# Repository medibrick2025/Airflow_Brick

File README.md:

# Airflow / Spiro Brick

The Spiro Brick interfaces with the [Sensirion SFM3300-D](https://sensirion.com/products/catalog/SFM3300-D) airflow sensor. It also enables airway pressure measurement using Amphenol differential pressure sensor such as [ELVH-family](https://allsensors.com/en/product-listing?family=elvh) with I2C 3.3V or 5V interface.

- [Datasheet SFM3300](./datasheets/Sensirion_Datasheet_SFM3300-AW_SFM3300-D.pdf)
- [Datasheet ELVH Family](./datasheets/DS-0376.pdf)

Example differential pressure sensor with I2C and 5V interface: ELVH-M160D-HRRD-C-N2A5 for 1/16 ID 1/8 OD tubing.

## Documentation

- [Education Background](./spirometer%20educational%20background/)
- [Assembly Instructions](./Spirometer%20Mechanical%20Design%20And%20Mechanical%20Assembly/)
- [Software / Firmware](./Spirometer%20Software/)

## SFM3300

- [Cleaning](./datasheets/Sensirion_GF_AN_SFM-21_Cleaning_Methods_D1.pdf)
- [Eval Kit](./datasheets/Sensirion_GF_AN_SFM-22_ClipOn_CapCable_Evaluation_Kit_D1_1.pdf)
- [Arduino Driver Sensirion](https://github.com/Sensirion/arduino-i2c-sfm3000) with [Sensirion Arduino Core](https://github.com/Sensirion/arduino-core)
- [Arduino Driver Alternative](https://github.com/MyElectrons/sfm3300-arduino)
 
## Spiro Brick PCB Design

The following files were created for this project using KiCad.

[View schematics as PDF](./KiCad/Altekreeti/Spiro_Brick.pdf)

## LiPo to 5V Power Boost

- [Ti TPS61090 Eval](./reference_designs/TPS61090_sbvu003.pdf)
- [Adafruit](https://learn.adafruit.com/adafruit-powerboost-500-plus-charger/downloads)

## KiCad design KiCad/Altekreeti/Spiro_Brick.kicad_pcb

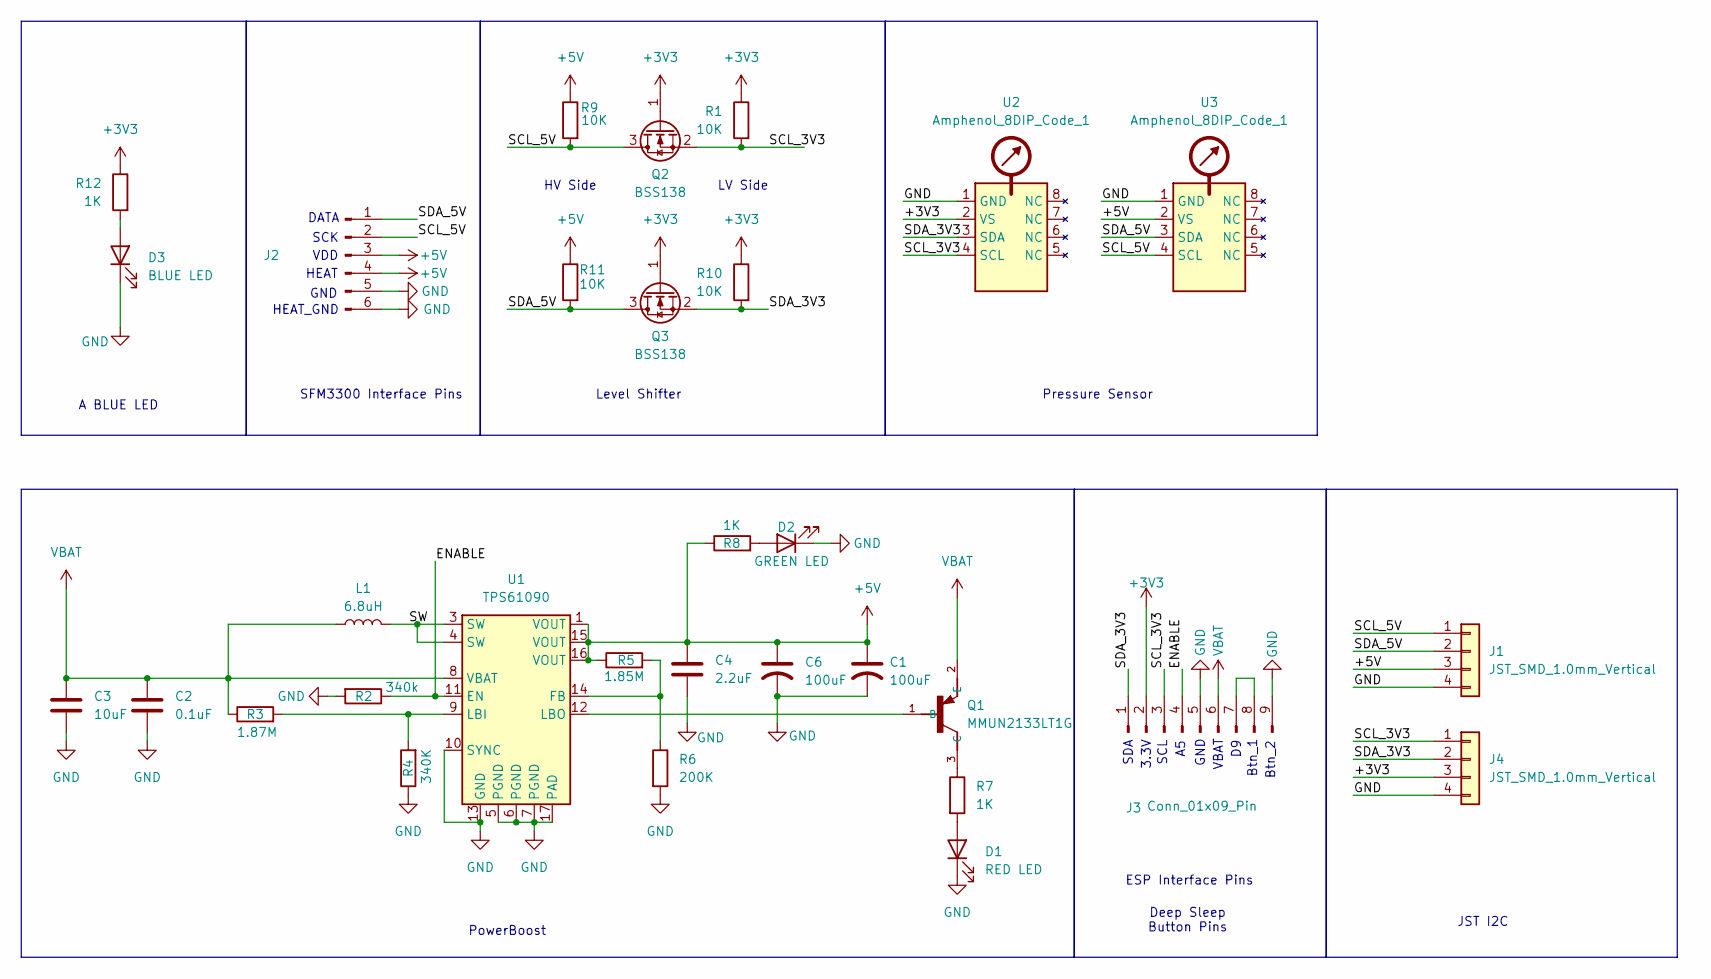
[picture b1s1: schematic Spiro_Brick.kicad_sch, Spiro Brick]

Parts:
C1, C6: 100uF; C_1210_3225Metric_Pad1.33x2.70mm_HandSolder
C2: 0.1uF; C_0805_2012Metric_Pad1.18x1.45mm_HandSolder
C3: 10uF; C_0805_2012Metric_Pad1.18x1.45mm_HandSolder
C4: 2.2uF; C_0805_2012Metric_Pad1.18x1.45mm_HandSolder
D1: RED LED; LED_0805_2012Metric
D2: GREEN LED; LED_0805_2012Metric
D3: BLUE LED; LED_0805_2012Metric
J1, J4: JST_SMD_1.0mm_Vertical; JST_1x04_P1.0mm_Vertical_SMD
J2: PinHeader_1x06_P2.54mm_Vertical
J3: Conn_01x09_Pin; PinHeader_1x09_P2.54mm_Vertical
L1: 6.8uH; L_Changjiang_FNR5045S
Q1: MMUN2133LT1G; SOT95P240X111-3N
Q2, Q3: BSS138; SOT-23
R1, R9, R10, R11: 10K; R_0805_2012Metric_Pad1.20x1.40mm_HandSolder
R2: 340k; R_0805_2012Metric_Pad1.20x1.40mm_HandSolder
R3: 1.87M; R_0805_2012Metric_Pad1.20x1.40mm_HandSolder
R4: 340K; R_0805_2012Metric_Pad1.20x1.40mm_HandSolder
R5: 1.85M; R_0805_2012Metric_Pad1.20x1.40mm_HandSolder
R6: 200K; R_0805_2012Metric_Pad1.20x1.40mm_HandSolder
R7, R8, R12: 1K; R_0805_2012Metric_Pad1.20x1.40mm_HandSolder
U1: TPS61090; Texas_RSA_VQFN-16-1EP_4x4mm_P0.65mm_EP2.7x2.7mm_ThermalVias
U2, U3: Amphenol_8DIP_Code_1; Amphenol_DIP-8_W13.08mm

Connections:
+3V3: J3.2, J4.3, Q2.1 (G), Q3.1 (G), R1.1, R10.1, R12.1, U2.2 (VS)
+5V: C1.1, C4.1, C6.1, J1.3, J2.3, J2.4, R5.1, R8.1, R9.1, R11.1, U1.1 (VOUT), U1.15 (VOUT), U1.16 (VOUT), U3.2 (VS)
/ENABLE: J3.4, R2.1, U1.11 (EN)
/SCL_3V3: J3.3, J4.1, Q2.2 (S), R1.2, U2.4 (SCL)
/SCL_5V: J1.1, J2.2, Q2.3 (D), R9.2, U3.4 (SCL)
/SDA_3V3: J3.1, J4.2, Q3.2 (S), R10.2, U2.3 (SDA)
/SDA_5V: J1.2, J2.1, Q3.3 (D), R11.2, U3.3 (SDA)
/SW: L1.2, U1.3 (SW), U1.4 (SW)
GND: C1.2, C2.2, C3.2, C4.2, C6.2, D1.1 (K), D2.1 (K), D3.1 (K), J1.4, J2.5, J2.6, J3.5, J3.9, J4.4, R2.2, R4.1, R6.2, U1.5 (PGND), U1.6 (PGND), U1.7 (PGND), U1.10 (SYNC), U1.13 (GND), U1.17 (PAD), U2.1 (GND), U3.1 (GND)
unnamed: D1.2 (A), R7.2
unnamed: D2.2 (A), R8.2
unnamed: D3.2 (A), R12.2
unnamed: J3.7, J3.8
unnamed: Q1.1 (B), U1.12 (LBO)
unnamed: Q1.3 (C), R7.1
unnamed: R5.2, R6.1, U1.14 (FB)
unnamed: R3.2, R4.2, U1.9 (LBI)
VBAT: C2.1, C3.1, J3.6, L1.1, Q1.2 (E), R3.1, U1.8 (VBAT)

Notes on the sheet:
HEAT
SDA
ESP Interface Pins
SFM3300 Interface Pins
Level Shifter
SCK
SCL
HV Side
Deep Sleep Button Pins
Btn_1
Btn_2
LV Side
DATA
Pressure Sensor
GND
VBAT
PowerBoost
A BLUE LED
3.3V
VDD
JST I2C
HEAT_GND

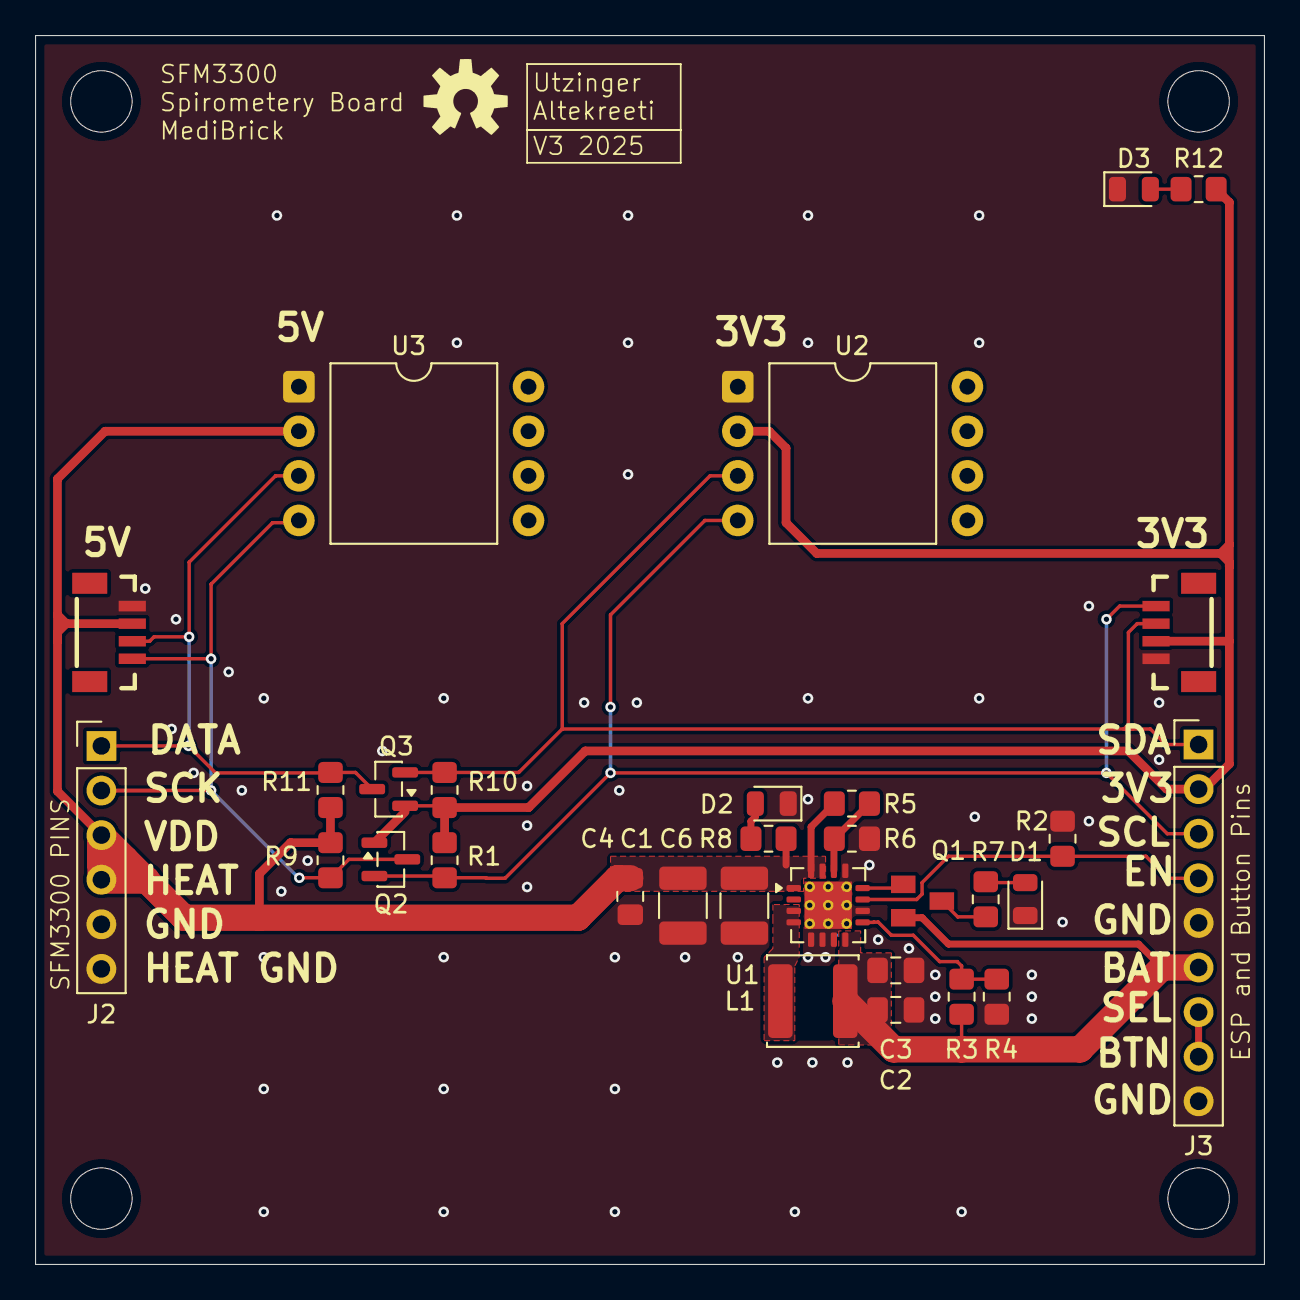
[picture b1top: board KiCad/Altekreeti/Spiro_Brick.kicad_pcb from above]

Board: 2 copper layers, 70.0 x 70.0 mm, 31 parts (0 on the bottom side), 18 nets.

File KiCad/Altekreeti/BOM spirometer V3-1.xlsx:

Item # | Designator | Qty | Manufacturer | Mfg Part # | LCSC Part# | U.S. Distributor | Description / Value | Packaging | Type | Cost | Designation | Footprint | Remark
1 | Q2,Q3 | 2 | onsemi | BSS138 | C52895 |  | N-Channel 50V 0.22A 0.36W Surface Mount SOT-23 | SOT-23 | SMD | 6.1199999999999997E-2 | BSS138 | SOT-23
2 | C1,C6 | 2 | YAGEO | CC1210MKX5R6BB107 | C723734 |  | 100uF ±20% 10V Ceramic Capacitor X5R 1210 | 1210 | SMD | 0.67759999999999998 | 100uF | C_1210_3225Metric_Pad1.33x2.70mm
3 | R7,R8,R12 | 2 | YAGEO | RC0805FR-071KL | C95781 |  | RES 1kΩ ±1% 125mW 0805 | 805 | SMD | 2E-3 | 1K | R_0805_2012Metric_Pad1.20x1.40mm
4 | L1 | 1 | cjiang | FNR5040S6R8MT | C167965 |  | 6.8uH Magnetic Shielded Inductor 3.4A SMD,5x5mm Fixed Inductors RoHS | 5x5mm | SMD | 9.3299999999999994E-2 | 6.8uH | L_Changjiang_FNR5045S
5 | C4 | 1 | YAGEO | CC0805KKX5R8BB225 | C277526 |  | 2.2uF ±10% 25V Ceramic Capacitor X5R 0805 | 805 | SMD | 1.84E-2 | 2.2uF | C_0805_2012Metric_Pad1.18x1.45mm
6 | D2 | 1 | XINGLIGHT | XL-2012UGC | C965815 |  | Green LED | 805 | SMD | 5.7000000000000002E-3 | GRN | LED_0805_2012Metric_GREEN_COLOR
7 | R4 | 1 | YAGEO | RC0805FR-07340KL | C137543 |  | RES 340kΩ ±1% 125mW | 805 | SMD | 2.0999999999999999E-3 | 340K | R_0805_2012Metric_Pad1.20x1.40mm
8 | R2 | 1 | YAGEO | RC0805FR-07100KL | C96346 |  | RES 100kΩ ±1% 125mW 0805 | 805 | SMD | 2.5000000000000001E-3 | 100k | R_0805_2012Metric_Pad1.20x1.40mm
9 | C3 | 1 | Samsung Electro-Mechanics | CL21A106KBYQNNE | C2932476 |  | 10uF ±10% 50V Ceramic Capacitor X5R 0805 | 805 | SMD | 4.1399999999999999E-2 | 10uF | C_0805_2012Metric_Pad1.18x1.45mm
10 | R5 | 1 | Walsin | WR08W1804FTL | C170816 |  | RES 1.8MΩ ±1% 125mW 0805 | 805 | SMD | 5.4000000000000003E-3 | 1.80M | R_0805_2012Metric_Pad1.20x1.40mm
11 | Q1 | 1 | onsemi | MMUN2133LT1G | C86182 |  | Pre-Biased Bipolar Transistor (BJT) 50V 100mA 246mW Surface Mount SOT-23 | SOT-23 | SMD | 3.0599999999999999E-2 | MMUN2133LT1G | SOT95P240X111-3N
12 | R11,R9,R1,R10 | 4 | YAGEO | RC0805FR-0710KL | C84376 |  | RES 10kΩ ±1% 125mW | 805 | SMD | 1.9E-3 | 10K | R_0805_2012Metric_Pad1.20x1.40mm
13 | R3 | 1 | Walsin | WR08W1874FTL | C367830 |  | RES 1.87MΩ ±1% 125mW 0805 | 805 | SMD | 5.3E-3 | 1.87M | R_0805_2012Metric_Pad1.20x1.40mm
14 | U1 | 1 | TI | TPS61030RSAR | C10110 |  | 600kHz Boost Adjustable 1.8V~5.5V 1A QFN-16-EP(4x4) Voltage Regulators - DC DC 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 | QFN-16-EP(4x4) | SMD | 1.6899 | TPS61090 | Texas_RSA_VQFN-16-1EP_4x4mm_P0.65mm_EP2.7x2.7mm_ThermalVias
15 | D1 | 1 | XINGLIGHT | XL-2012SURC | C965812 |  | RED LED | 805 | SMD | 5.8999999999999999E-3 | RED LED | LED_0805_2012Metric_RED_COLOR
16 | R6 | 1 | YAGEO | RT0805BRD07200KL | C728645 |  | RES 200kΩ ±0.1% 125mW 0805 | 805 | SMD | 3.3599999999999998E-2 | 200K | R_0805_2012Metric_Pad1.20x1.40mm
17 | C2 | 1 | YAGEO | CC0805KRX7R8BB104 | C519981 |  | 100nF ±10% 25V Ceramic Capacitor X7R 0805 | 805 | SMD | 5.8999999999999999E-3 | 100nF | C_0805_2012Metric_Pad1.18x1.45mm
18 | D3 | 1 | XINGLIGHT | XL-2012UBC | C965817 |  | Blue LED | 805 | SMD | 6.4000000000000003E-3 | BLUE LED | LED_0805_2012Metric
19 | J1,J4 | 2 | JST | BM04B-SRSS-TBT(LF)(SN) | C495539 |  | Connector Header 4 position 1mm Pitch 1A Surface Mount,Vertical -25℃~+85℃ | SMD,P=1mm | SMD | 0.31240000000000001 | JST_I2C | JST_SMD_1.0mm_Vertical
20 | J3 | 1 |  |  |  |  | Do not Place |  |  |  | Conn_01x09_Pin | PinHeader_1x09_P2.54mm_Vertical | Do not Place
21 | J2 | 1 |  |  |  |  | Do not Place |  |  |  | ~ | PinHeader_1x06_P2.54mm_Vertical | Do not Place

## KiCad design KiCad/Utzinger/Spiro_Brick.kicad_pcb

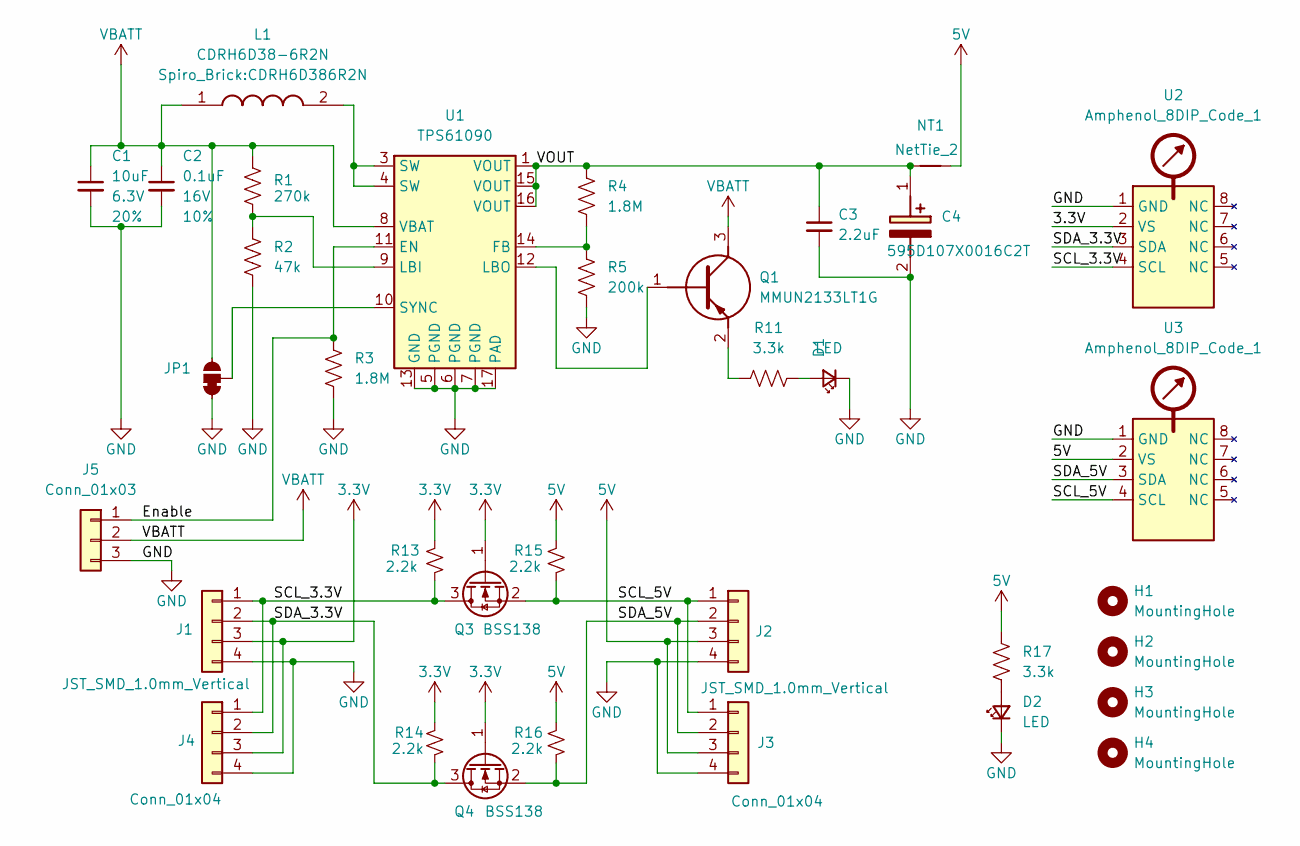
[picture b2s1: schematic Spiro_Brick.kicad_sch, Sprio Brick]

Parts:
C1: 10uF; C_0402_1005Metric; Voltage 6.3V; Tolerance 20%
C2: 0.1uF; C_0402_1005Metric; Voltage 16V; Tolerance 10%
C3: 2.2uF; C_0402_1005Metric; Voltage 10V; Tolerance 10%
C4: 595D107X0016C2T; CAPPC5932X280N; Manufacturer_Part_Number 595D107X0016C2T; Mouser Part Number 74-595D107X0016C2T
D1, D2: LED; LED_0402_1005Metric
H1, H2, H3, H4: MountingHole; MountingHole_3.2mm_M3
J1, J2: JST_SMD_1.0mm_Vertical; JST_1x04_P1.0mm_Vertical_SMD
J3, J4: Conn_01x04; PinHeader_1x04_P2.54mm_Vertical
J5: Conn_01x03; PinHeader_1x03_P2.54mm_Vertical
JP1: SolderJumper-3_P1.3mm_Bridged12_Pad1.0x1.5mm
L1: CDRH6D38-6R2N; CDRH6D386R2N; Manufacturer_Part_Number CDRH6D38-6R2N
NT1: NetTie_2; NetTie-2_SMD_Pad2.0mm
Q1: MMUN2133LT1G; SOT96P237X111-3N; Manufacturer_Part_Number MMUN2133LT1G; Mouser Part Number 863-MMUN2133LT1G
Q3, Q4: BSS138; SOT-23
R1: 270k; R_0402_1005Metric
R2: 47k; R_0402_1005Metric
R3, R4: 1.8M; R_0402_1005Metric
R5: 200k; R_0402_1005Metric
R11, R17: 3.3k; R_0402_1005Metric
R13, R14, R15, R16: 2.2k; R_0402_1005Metric
U1: TPS61090; Texas_RSA_VQFN-16-1EP_4x4mm_P0.65mm_EP2.7x2.7mm_ThermalVias
U2, U3: Amphenol_8DIP_Code_1; Amphenol_DIP-8_W13.08mm

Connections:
3.3V: J1.3, J4.3, Q3.1 (G), Q4.1 (G), R13.2, R14.2, U2.2 (VS)
5V: J2.3, J3.3, NT1.2, R15.2, R16.2, R17.1, U3.2 (VS)
/Enable: J5.1, R3.1, U1.11 (EN)
/SCL_3.3V: J1.1, J4.1, Q3.3 (D), R13.1, U2.4 (SCL)
/SCL_5V: J2.1, J3.1, Q3.2 (S), R15.1, U3.4 (SCL)
/SDA_3.3V: J1.2, J4.2, Q4.3 (D), R14.1, U2.3 (SDA)
/SDA_5V: J2.2, J3.2, Q4.2 (S), R16.1, U3.3 (SDA)
/VOUT: C3.1, C4.1 (+), NT1.1, R4.1, U1.1 (VOUT), U1.15 (VOUT), U1.16 (VOUT)
GND: C1.2, C2.2, C3.2, C4.2 (-), D1.1 (K), D2.1 (K), J1.4, J2.4, J3.4, J4.4, J5.3, JP1.1 (A), R2.2, R3.2, R5.2, U1.5 (PGND), U1.6 (PGND), U1.7 (PGND), U1.13 (GND), U1.17 (PAD), U2.1 (GND), U3.1 (GND)
unnamed: D1.2 (A), R11.2
unnamed: D2.2 (A), R17.2
unnamed: JP1.2 (B), U1.10 (SYNC)
unnamed: L1.2, U1.3 (SW), U1.4 (SW)
unnamed: Q1.1 (B), U1.12 (LBO)
unnamed: Q1.2 (E), R11.1
unnamed: R4.2, R5.1, U1.14 (FB)
unnamed: R1.2, R2.1, U1.9 (LBI)
VBATT: C1.1, C2.1, J5.2, JP1.3 (C), L1.1, Q1.3 (C), R1.1, U1.8 (VBAT)

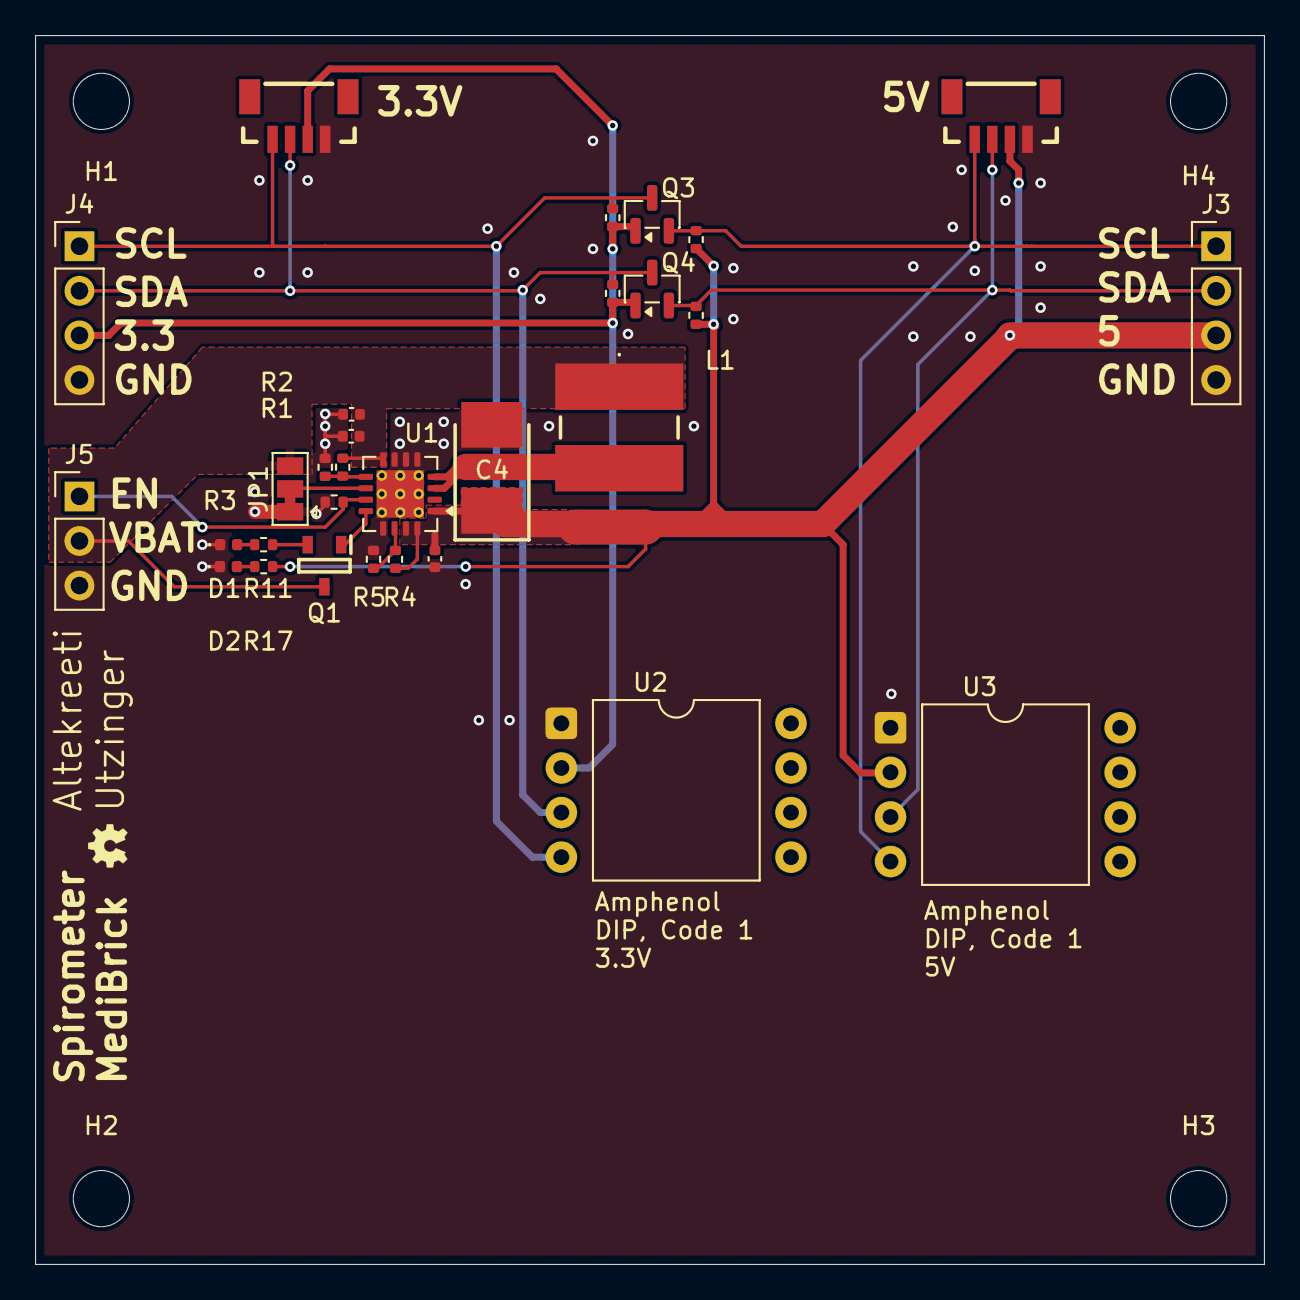
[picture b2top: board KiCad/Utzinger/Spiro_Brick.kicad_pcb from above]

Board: 2 copper layers, 70.0 x 70.0 mm, 36 parts (0 on the bottom side), 18 nets.

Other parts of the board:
Ref**: Val**; OSHW_Logo_2.5mm

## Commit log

2026-01-06 Fix inductor ground loop
2026-01-18 11111111
2026-01-18 test
2026-01-23 Education Background Update
2026-02-02 A line of blank space was deleted.
2026-02-02 Education Background reorgnize, add two folders
2026-02-10 Added setup
2026-02-11 Re-edited the setup, optimized the formatting, and uploaded the code.
2026-05-06 Add Faceplate Assembly
2026-05-06 Add User Manual
2026-05-06 Add source
